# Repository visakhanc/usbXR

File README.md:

usbXR - Low cost USB Wireless transceiver
=========================================

usbXR is basically a USB adapter for the RFM75 2.4GHz wireless module. The USB functionality is implemented using AVR ATmega328 and the [v-usb](https://www.obdev.at/products/vusb/index.html) firmware-only USB driver for AVRs, which emulates USB low-speed protocol. The device can be used for bi-directional communication with *remote* nodes, containing the same wireless module (ie. RFM75 or other compatible modules like RFM70/RFM73).

Once the [HID-Bootloader](https://github.com/visakhanc/usbXR/tree/master/bootloader/HID-bootloader-mega328) is flashed, you can load your application to usbXR using a command-line utility. In addition you can program remote node AVRs over-the-air! Both remote and self programming uses a single command line application bootloadHID:

`bootloadHID.exe receiver.hex` - programs usbXR device with _receiver.hex_

`bootloadHID.exe remote transmitter.hex` - programs a remote node with _transmitter.hex_

`bootloadHID.exe -r test.hex` - programs usbXR with _test.hex_ and resets usbXR
	
For over-the-air programming, the remote AVR need to be initially programmed with a bootloader. An example for ATmega8 is given [here](https://github.com/visakhanc/usbXR/tree/master/bootloader/remote-bootloader-mega8).
	
[applications](https://github.com/visakhanc/usbXR/tree/master/applications) directory contains example applications.

Hardware
--------

The hardware is simple and can only cost as low as 5 USD to make. [hardware](https://github.com/visakhanc/usbXR/tree/master/hardware) directory contains the eagle schematic and layout with Partlist.
You can order the PCBs from [OSHpark](https://oshpark.com/shared_projects/8Y8Vg5b4).

Setup
-----

HID bootloader need to be programmed to the AVR to make use of self and remote programming over USB. The bootloader and the command-line utility is an extension to the official HID [bootloader](https://www.obdev.at/products/vusb/bootloadhid.html) from v-usb, modified to incorporate remote bootloading functionality. 

**IMPORTANT:** Before building any AVR projects from this repository, [common-libs](https://github.com/visakhanc/common_libs) repository needs to be downloaded first. This contains many device libraries for AVRs such as RFM70 etc. Download it and rename the directory to 'common'. Downloaded repositories must be at same directory level for Makefile to work. That is:

	AVR_Projects/
	|
	|-- common/
	|
	|-- usbXR/

#### Bootloader

For building the bootloader firmware under Windows, WinAVR is needed. To flash the AVR, after the hardware is ready, connect an ISP programmer like USBasp to the 6 ISP pins of usbXR. Make sure to provide only 3.3v target voltage from the programmer. 5v would damage the RFM70 transceiver. To compile and program the HID-Bootloader, go into the bootloader directory and execute these steps:

1. make clean
2. make all
3. make fuse
4. make program

*If any ISP programmer other than USBasp is used, change the Makefile accordingly.*

Now, plug usbXR into a USB port while pressing down the button, and it will be recognized as an HID device (HIDBoot).

#### Bootloader utility

You will need MinGW installation to compile under Windows. To compile BootloadHID application under Windows, execute:

	make -f Makefile.windows
	
To use the bootloader, plug-in the device to a USB port while pressing down the button. The LED will be on and it is now in bootloader mode. Now use the BootloadHID application as explained earlier, to self or remote programming.

#### Remote bootloader

If you want to use the over-the-air programming feature of usbXR, a bootloader need to be initially programmed to the AVR. The example given is for ATmega8, but can be used for other AVRs with at least 2kB of boot space. The bootloader uses the last byte of the AVR EEPROM to store a validity flag. View the readme for building instructions. A button and LED is expected for a remote device. To enter bootloader, the button needs to be pressed while powering-on or resetting the AVR. Now, the bootloadHID tool can be used for programming. The LED flashes at 1 sec interval, when over-the-air programming is in progress until the programming is over. If programming fails midway, the command needs to be repeated. Programming is successful only when the LED stops flashing.

Applications
------------

An [example](https://github.com/visakhanc/usbXR/tree/master/applications/SensorReceive) shows a remote node sending 3 axis accelerometer values from MPU6050 sensor, continuously to usbXR and plotting the values in real-time. Here, interrupt-in endpoint is used to transfer the received samples over USB, at intervals as short as 10ms. Since it uses HID protocol, no driver is required under Windows. A WPF C# application is used to get USB packets and draw the graph. 

A video showing this example is [here](https://www.youtube.com/watch?v=QmQyY-55VSc).

Please visit [v-usb](https://www.obdev.at/products/vusb/index.html) for more details of implementating USB devices using v-usb library. For easy access of USB device, PyUSB python library can be used.

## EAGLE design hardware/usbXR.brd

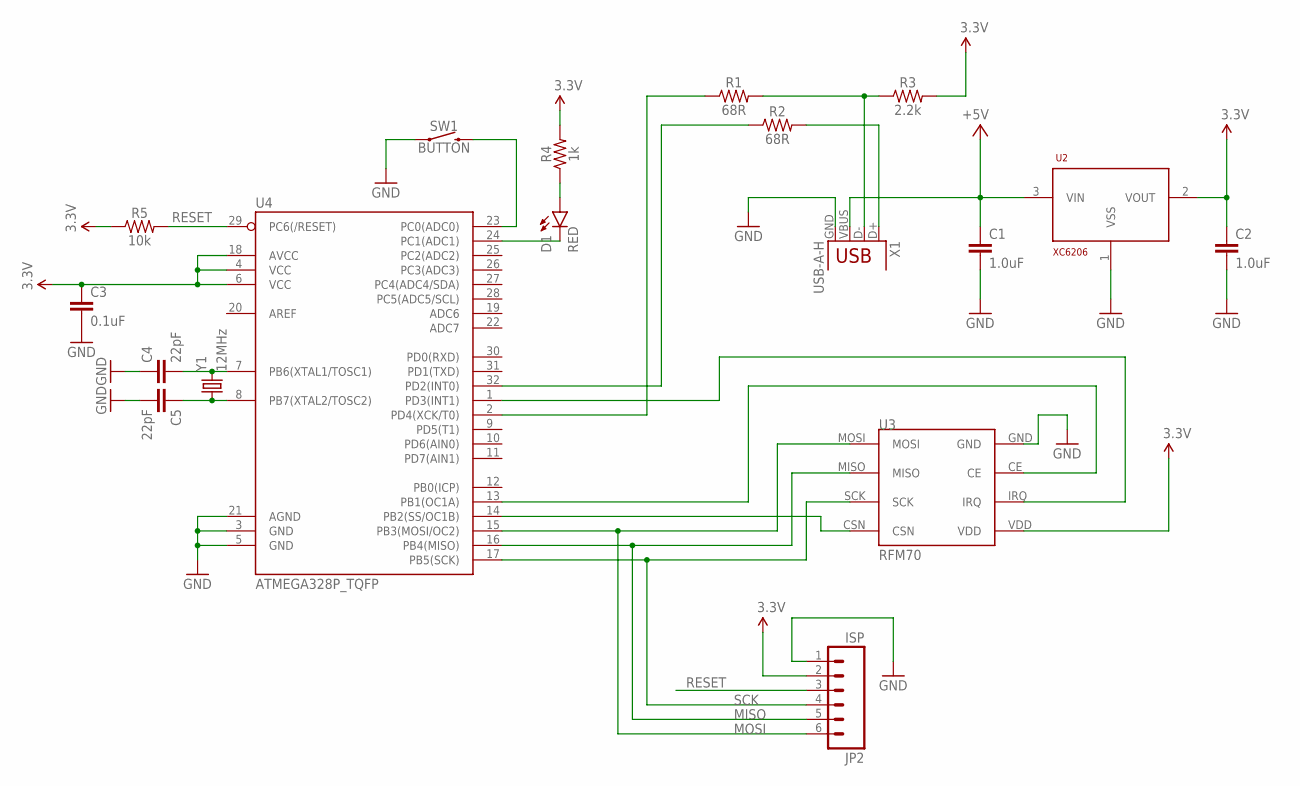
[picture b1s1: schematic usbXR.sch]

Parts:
C1, C2: 1.0uF; 0603
C3: 0.1uF; 0603
C4, C5: 22pF; 0603
D1: RED; LED-1206
JP2: ISP; 1X06-SMD_EDGE
R1, R2: 68R; 0603
R3: 2.2k; 0603
R4: 1k; 0603
R5: 10k; 0603
SW1: BUTTON; TACTILE_SWITCH_3X4MM
U2: XC6206; SOT23-3
U3: RFM70; RFM70_SMD
U4: ATMEGA328P_TQFP; TQFP32-08
X1: USB-A-H
Y1: 12MHz; HC49US

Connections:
3.3V: C2.1, C3.1, JP2.2, R3.2, R4.2, R5.1, U2.2 (VOUT), U3.VDD, U4.4 (VCC), U4.6 (VCC), U4.18 (AVCC)
+5V: C1.1, U2.3 (VIN), X1.VBUS
CE: U3.CE, U4.13 (PB1(OC1A))
CSN: U3.CSN, U4.14 (PB2(SS/OC1B))
GND: C1.2, C2.2, C3.2, C4.1, C5.2, JP2.1, SW1.1, U2.1 (VSS), U3.GND, U4.3 (GND), U4.5 (GND), U4.21 (AGND), X1.GND
IRQ: U3.IRQ, U4.1 (PD3(INT1))
LED: D1.C, U4.24 (PC1(ADC1))
MISO: JP2.5, U3.MISO, U4.16 (PB4(MISO))
MOSI: JP2.6, U3.MOSI, U4.15 (PB3(MOSI/OC2))
unnamed: R1.2, R3.1, X1.D-
unnamed: R2.2, X1.D+
unnamed: D1.A, R4.1
unnamed: C4.2, U4.7 (PB6(XTAL1/TOSC1)), Y1.2
unnamed: C5.1, U4.8 (PB7(XTAL2/TOSC2)), Y1.1
RESET: JP2.3, R5.2, U4.29 (PC6(/RESET))
SCK: JP2.4, U3.SCK, U4.17 (PB5(SCK))
SW: SW1.2, U4.23 (PC0(ADC0))
USB_DM: R1.1, U4.2 (PD4(XCK/T0))
USB_DP: R2.1, U4.32 (PD2(INT0))

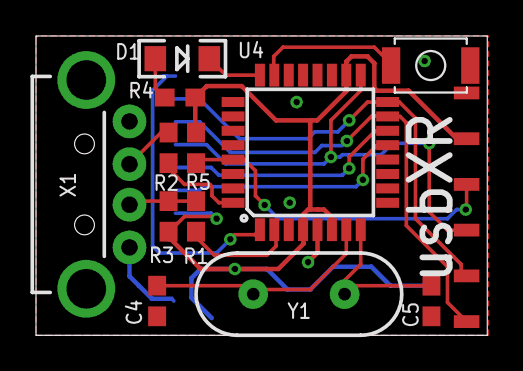
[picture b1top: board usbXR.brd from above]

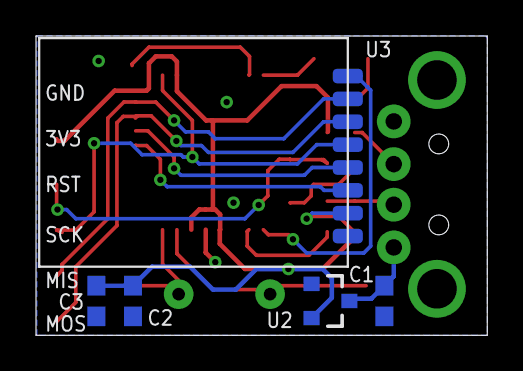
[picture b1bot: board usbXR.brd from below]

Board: 2 copper layers, 25.1 x 16.6 mm, 18 parts (5 on the bottom side), 19 nets.

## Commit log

2017-11-18 Initial commit with only hardware and intro
2017-11-18 Modified README
2017-11-19 schematic pdf added
2017-11-20 Bootloader added
2017-11-20 Applications added
2017-11-20 README updated
2017-11-20 Added example schematic for remote
2017-11-20 SChematic added for example application
2017-11-20 schematic removied
2017-11-20 README update
2017-11-21 schematic in PNG
2017-11-21 pics added
2017-11-21 pic added
2019-01-27 README change
2019-04-02 Included spi_config.h for applicable projects
2026-02-04 bootloadHID application update
2026-02-04 bootloader update
2026-02-14 rearranged bootloader directory
2026-02-14 board.h hardcoded inside bootloader_config.h

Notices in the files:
parts and their libraries:
SparkFun-Capacitors: Licensing: Creative Commons ShareAlike 4.0 International - https://creativecommons.org/licenses/by-sa/4.0
